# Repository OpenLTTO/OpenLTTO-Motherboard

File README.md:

# OpenLTTO
The OpenLTTO Project is an attempt to recreate the Lazer Tag Team Ops protocol, and game system, in a completely open-source solution. Eventually our intent, is to expand on the LTTO system, adding new functionality, and features, while maintaining backwards compatibility with this classic Lazer Tag gear.

> This Project wouldn't be possible without all the hard work of Richie Mickan https://github.com/rmick
> His work on recreating the LTTO Protocol, and the development of the Combobulator app are core to the firmware and capabilities of this project.

> Additionally this is built on top of the excellent product developed and released by Hasbro/Tiger Electronics. And the work done by Tag Ferret to release the technical specs, and unlock much of the magic of the protocol, and the inner workings.

We intend to do this via a collection of open-source hardware components that can act as building blocks, to build anything you might require for a Lazer Tag game (Taggers, Hosting Pods, Zone controllers, utilities, etc). And an opensource firmware to operate it all. 

Shield: [![CC BY-NC-SA 4.0][cc-by-nc-sa-shield]][cc-by-nc-sa]

This work is licensed under a
[Creative Commons Attribution-NonCommercial-ShareAlike 4.0 International License][cc-by-nc-sa].

[![CC BY-NC-SA 4.0][cc-by-nc-sa-image]][cc-by-nc-sa]

[cc-by-nc-sa]: http://creativecommons.org/licenses/by-nc-sa/4.0/
[cc-by-nc-sa-image]: https://licensebuttons.net/l/by-nc-sa/4.0/88x31.png
[cc-by-nc-sa-shield]: https://img.shields.io/badge/License-CC%20BY--NC--SA%204.0-lightgrey.svg

# OpenLTTO Motherboard
The OpenLTTO Motherboard is a simple circuit, which mainly breaks out connectors from an M5Stack CoreS3, which is a packaged microcontroller containing an ESP32-S3 chip. This microcontroller offers a suite of great features making it an ideal centerpiece for the OpenLTTO ecosystem. It is inexpensive, and provides a nice commercial product, with a display, touchscreen, motion sensors, sound output, an SD Card slot, and plenty of internal flash and RAM, along with a powerful dual core 240Mhz processor.

## Hardware Interfaces
The OpenLTTO Motherboard has multiple hardware interfaces that can be used in many ways to construct Lazer Tag gear

### IR Ports
The OpenLTTO Motherboard has 4x IR Ports, which allow interfacing any of our IR Modules. Each port can be individually addressed with independent IR Transmit and Receive functions in order to sense where incoming tags come from, and control where IR packets are sent. Modules can also be daisy chained together on a single port, which makes them function in unison at a single address (all modules include an "IN" and an "OUT" port to allow chaining)

### Switch Ports
The Switch ports allow interfacing buttons or switches to the motherboard, such as user interaction buttons, or trigger/reload switches, etc. These can then be mapped in the configuration screen to various functions.

### RGB Port
The RGB Port is a common pinout for interfacing WS2812 or similar RGB LED chains (often called NeoPixels). These can be chained together, and controlled from the firmware for a number of functions and lighting effects.

### I2C Expansion Port
The I2C Port is reserved for future expansion, it uses the common "Grove" pinout and connector (JST PH 2.0). This will allow adding any other I2C based peripherals in the future.

### Battery Connection
The Battery Connection supports any single parallel cell 3.7V Lithium Polymer, or Lithium Ion batteries (for example you can have a single cell, or you can hook up multiple cells in parallel, but never in series). The M5Stack CoreS3 has a USBC port and can manage battery levels, and charge the battery via USBC.

## OpenLTTO Motherboard Top Side (interface to M5Stack CoreS3)

## OpenLTTO Motherboard Bottom Side

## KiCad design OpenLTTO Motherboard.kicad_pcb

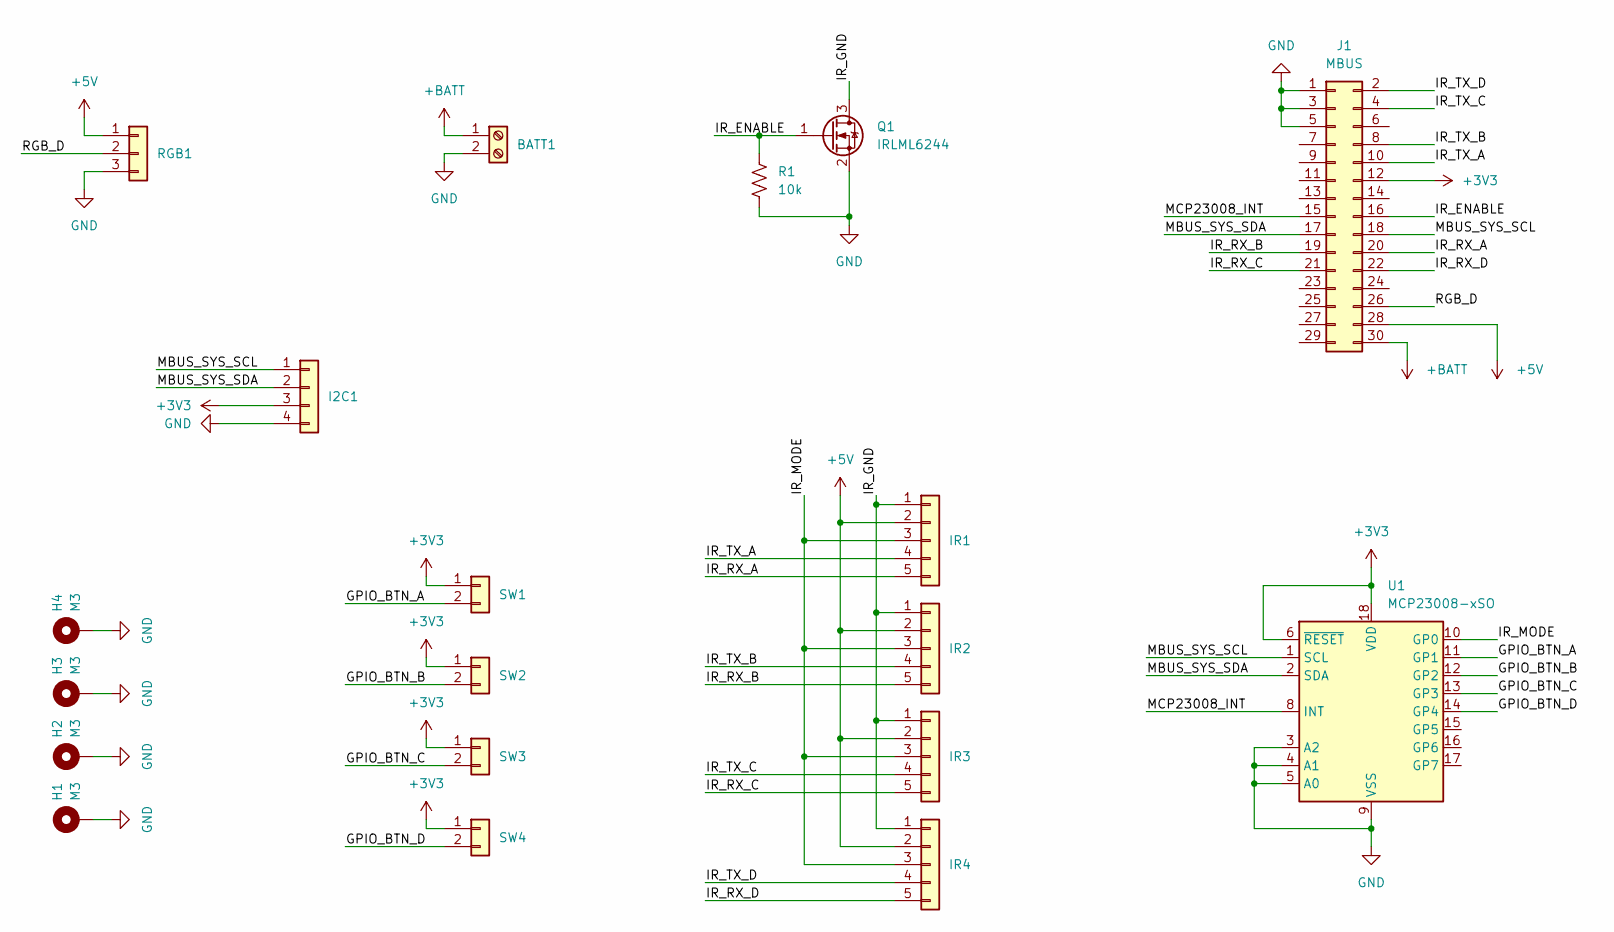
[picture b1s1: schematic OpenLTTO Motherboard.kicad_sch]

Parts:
BATT1: TerminalBlock_Phoenix_MKDS-1,5-2_1x02_P5.00mm_Horizontal
H1, H2, H3, H4: M3; MountingHole_3.2mm_M3_DIN965_Pad
I2C1: JST_PH_B4B-PH-K_1x04_P2.00mm_Vertical
IR1, IR2, IR3, IR4: JST_PH_B5B-PH-K_1x05_P2.00mm_Vertical
J1: MBUS; PinHeader_2x15_P2.54mm_Vertical
Q1: IRLML6244; SOT-23
R1: 10k; R_1206_3216Metric_Pad1.30x1.75mm_HandSolder
RGB1: JST_PH_B3B-PH-K_1x03_P2.00mm_Vertical
SW1, SW2, SW3, SW4: JST_PH_B2B-PH-K_1x02_P2.00mm_Vertical
U1: MCP23008-xSO; SOIC-18W_7.5x11.6mm_P1.27mm

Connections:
+3V3: I2C1.3, J1.12, SW1.1, SW2.1, SW3.1, SW4.1, U1.6 (~RESET), U1.18 (VDD)
+5V: IR1.2, IR2.2, IR3.2, IR4.2, J1.28, RGB1.1
+BATT: BATT1.1, J1.30
/GPIO_BTN_A: SW1.2, U1.11 (GP1)
/GPIO_BTN_B: SW2.2, U1.12 (GP2)
/GPIO_BTN_C: SW3.2, U1.13 (GP3)
/GPIO_BTN_D: SW4.2, U1.14 (GP4)
/IR_ENABLE: J1.16, Q1.1 (G), R1.1
/IR_GND: IR1.1, IR2.1, IR3.1, IR4.1, Q1.3 (D)
/IR_MODE: IR1.3, IR2.3, IR3.3, IR4.3, U1.10 (GP0)
/IR_RX_A: IR1.5, J1.20
/IR_RX_B: IR2.5, J1.19
/IR_RX_C: IR3.5, J1.21
/IR_RX_D: IR4.5, J1.22
/IR_TX_A: IR1.4, J1.10
/IR_TX_B: IR2.4, J1.8
/IR_TX_C: IR3.4, J1.4
/IR_TX_D: IR4.4, J1.2
/MBUS_SYS_SCL: I2C1.1, J1.18, U1.1 (SCL)
/MBUS_SYS_SDA: I2C1.2, J1.17, U1.2 (SDA)
/MCP23008_INT: J1.15, U1.8 (INT)
/RGB_D: J1.26, RGB1.2
GND: BATT1.2, H1.1, H2.1, H3.1, H4.1, I2C1.4, J1.1, J1.3, J1.5, Q1.2 (S), R1.2, RGB1.3, U1.3 (A2), U1.4 (A1), U1.5 (A0), U1.9 (VSS)

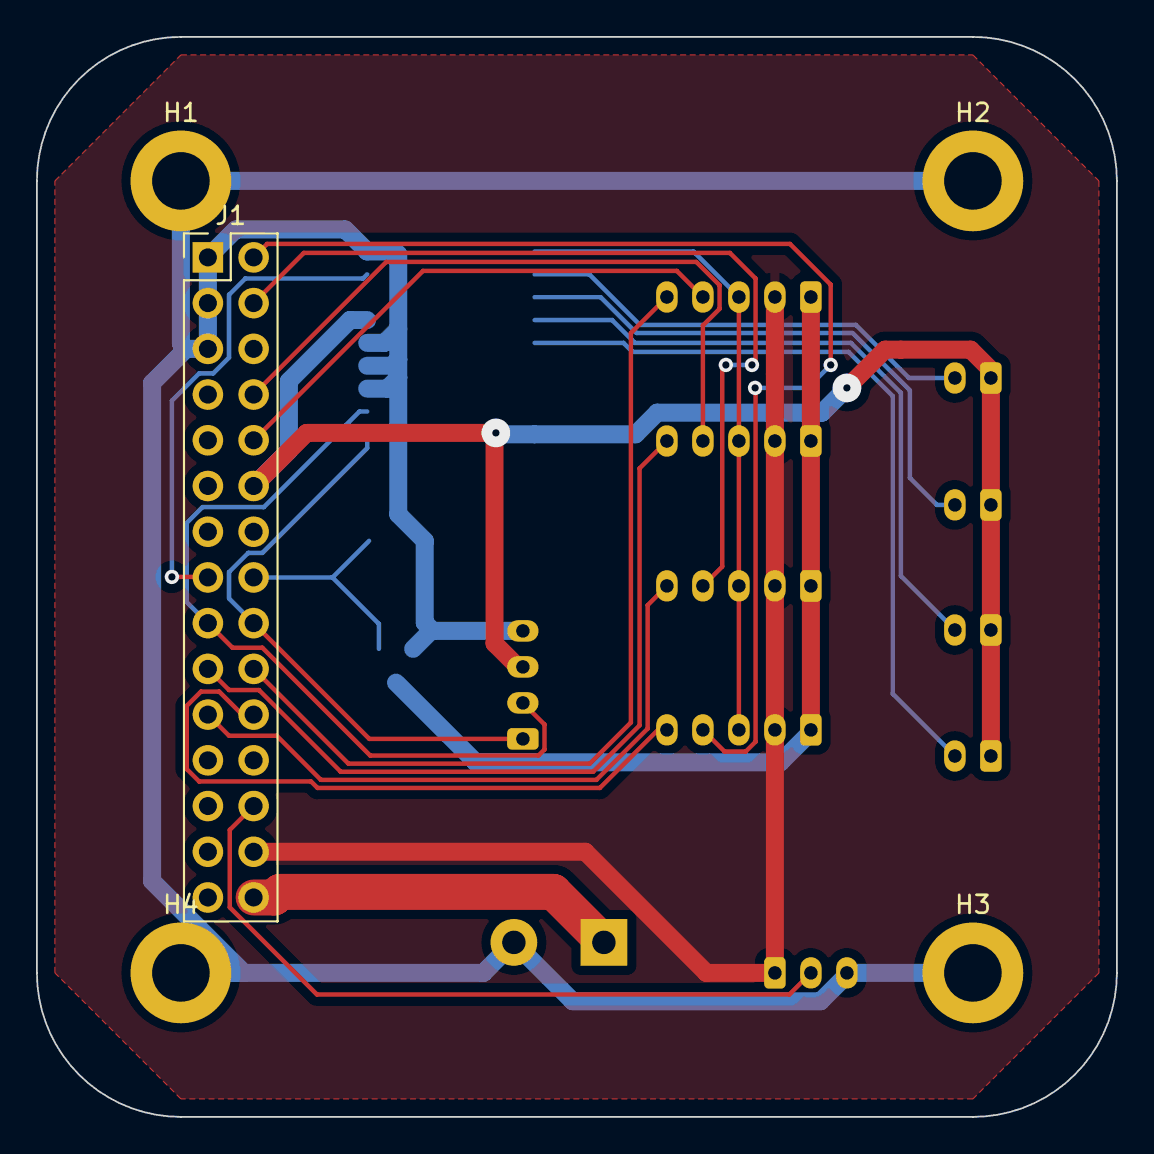
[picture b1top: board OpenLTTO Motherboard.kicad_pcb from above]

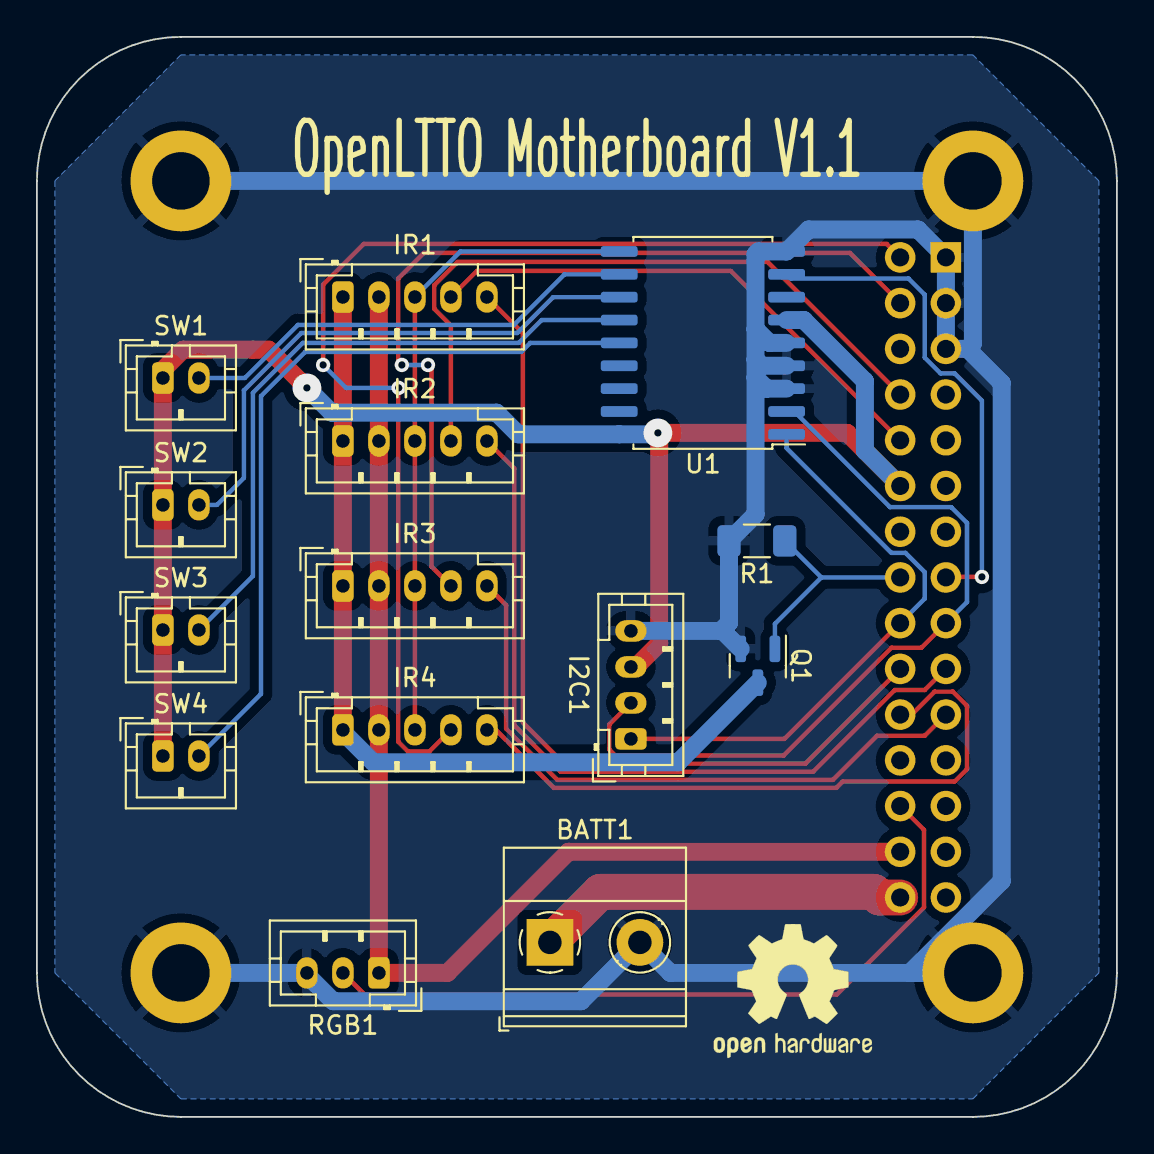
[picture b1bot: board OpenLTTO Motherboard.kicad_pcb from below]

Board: 2 copper layers, 60.0 x 60.0 mm, 19 parts (14 on the bottom side), 23 nets.

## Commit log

2024-02-01 Updated schematic metadata, and added PCB renders, and schematic PDF
2024-02-02 Updated Schematic to v1.1, added GPIO breakout and changed IR ports to all be independent. Also added I2C port, and added license, and updated readme
